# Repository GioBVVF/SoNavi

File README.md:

# SoNavi - Progetto del Comando Vigili del Fuoco di Padova
Apparato Bluetooth per il supporto alla navigazione delle squadre VVF. Progetto ideato e realizzato da Mirko Musto e Piero Grigolon.

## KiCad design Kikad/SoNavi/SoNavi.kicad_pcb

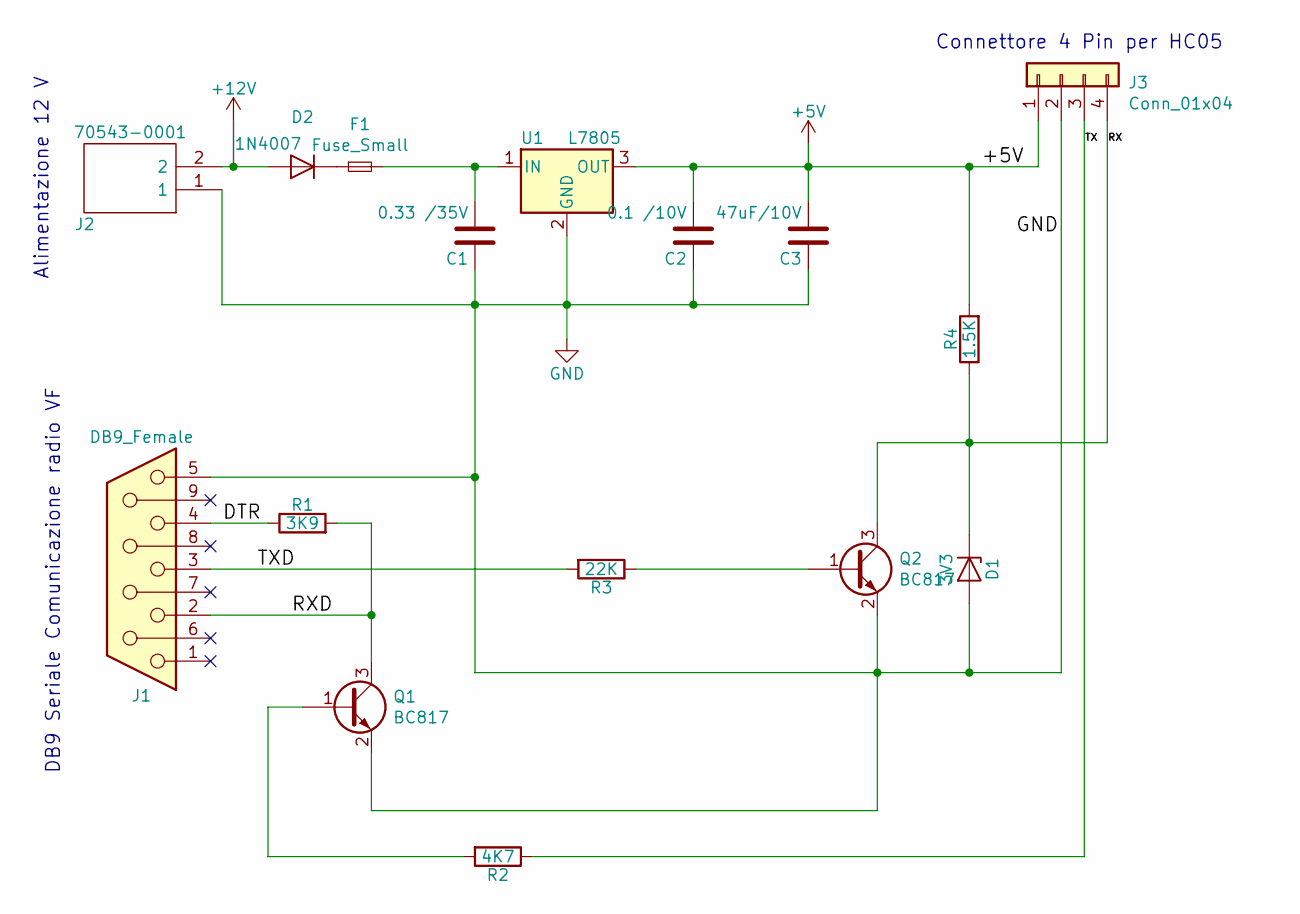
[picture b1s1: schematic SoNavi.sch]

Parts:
C1: 0.33 /35V; C_1206_3216Metric
C2: 0.1 /10V; C_1206_3216Metric
C3: 47uF/10V; CP_Radial_D5.0mm_P2.50mm
D1: 3V3; D_SOT-23_ANK
D2: 1N4007; D_SOD-123
F1: Fuse_Small; FUSC1608X64N
J1: DB9_Female; DSUB-9_Female_EdgeMount_P2.77mm
J2: 70543-0001; SHDR2W97P0X254_1X2_737X660X1194P; Manufacturer_Part_Number 70543-0001
J3: Conn_01x04; SHDR4W97P0X254_1X4_1271X660X1143P
Q1, Q2: BC817; SOT-23
R1: 3K9; R_0805_2012Metric
R2: 4K7; R_0805_2012Metric
R3: 22K; R_0805_2012Metric
R4: 1.5K; R_0805_2012Metric
U1: L7805; TO-252-3_TabPin2

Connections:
+5V: C2.2, C3.2, J3.1, R4.2, U1.3 (OUT)
+12V: D2.2 (A), J2.2
/DTR: J1.4, R1.1
/RX: D1.1 (K), J3.4, Q2.3 (C), R4.1
/RXD: J1.2, Q1.3 (C), R1.2
/TX: J3.3, R2.1
/TXD: J1.3, R3.2
GND: C1.1, C2.1, C3.1, D1.2 (A), J1.5, J2.1, J3.2, Q1.2 (E), Q2.2 (E), U1.2 (GND)
unnamed: C1.2, F1.2, U1.1 (IN)
unnamed: D2.1 (K), F1.1
unnamed: Q1.1 (B), R2.2
unnamed: Q2.1 (B), R3.1

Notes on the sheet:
Connettore 4 Pin per HC05
DB9 Seriale Comunicazione radio VF
Alimentazione 12 V

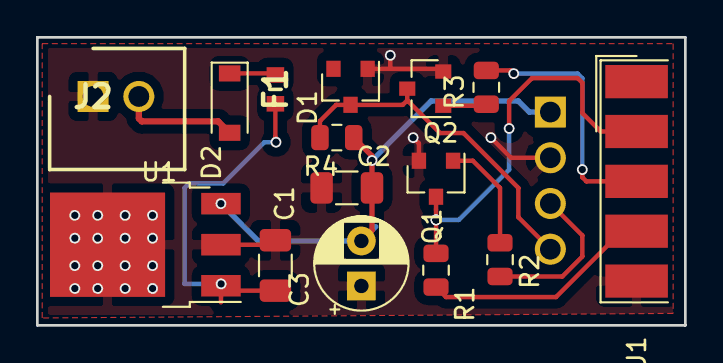
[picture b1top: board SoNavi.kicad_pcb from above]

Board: 2 copper layers, 36.0 x 16.0 mm, 16 parts (1 on the bottom side), 12 nets.

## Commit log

2018-12-07 Create Kikad
2018-12-07 Progetto Verificato
